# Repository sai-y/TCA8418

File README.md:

# TCA8418

My first PCB design based on Sparkfun's Qwiic connector system. It is an I<sup>2</sup>C based keypad controller. It is inspired by this [one](https://www.sparkfun.com/products/14660).

This repository contains the PCB design for now. Code coming soon.

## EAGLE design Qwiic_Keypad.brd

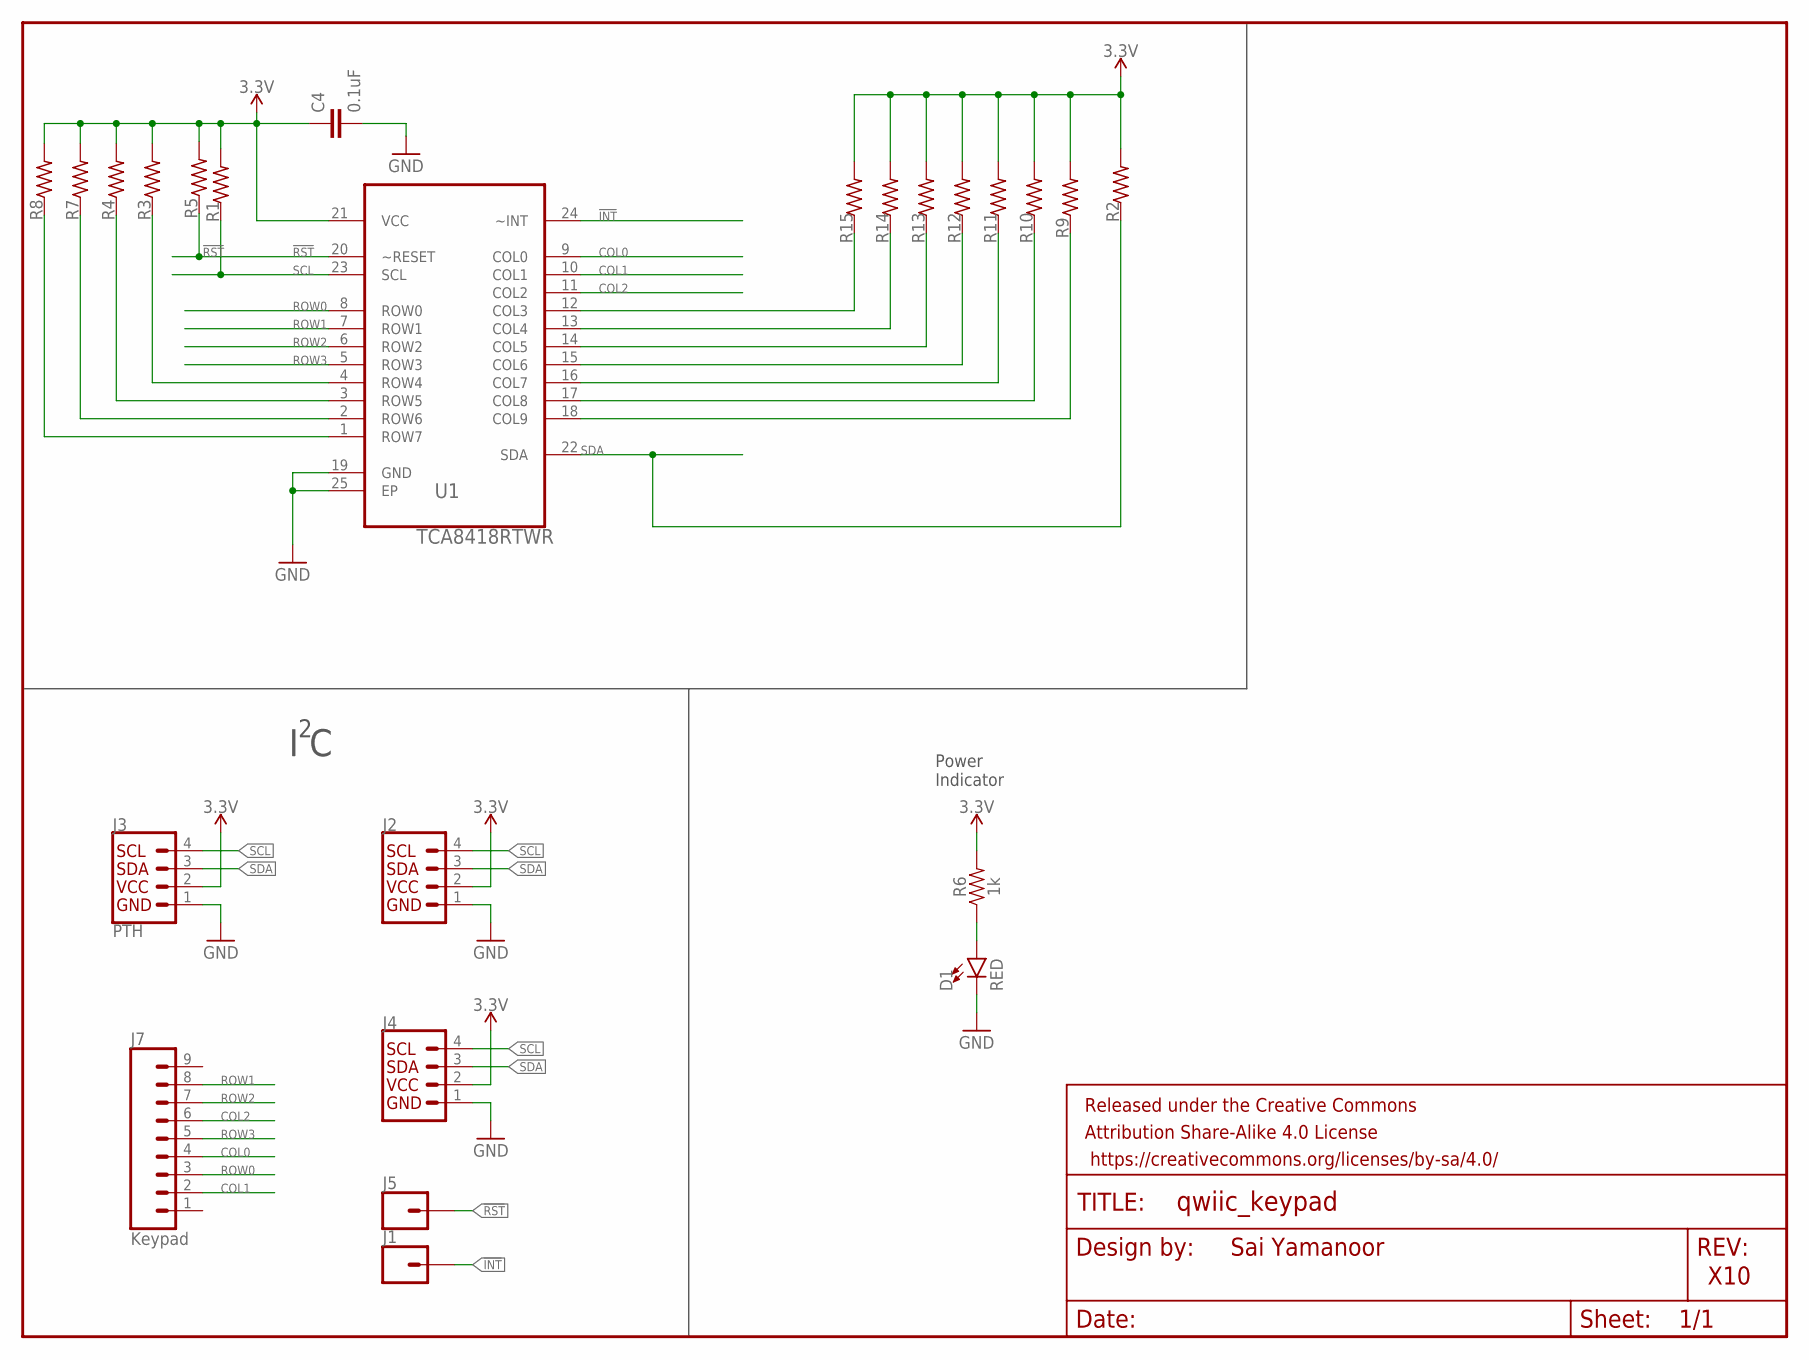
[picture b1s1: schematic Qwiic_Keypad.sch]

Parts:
C4: 0.1uF; 0603
D1: RED; LED-0603
FRAME1: FRAME-LETTER; CREATIVE_COMMONS
J1, J5: CONN_01PTH_NO_SILK_YES_STOP; 1X01_NO_SILK
J2, J4: QWIIC_CONNECTORJS-1MM; 1X04_1MM_RA
J3: PTH; 1X04_NO_SILK
J7: Keypad; 1X09_NO_SILK
R1, R2: 4.7k; R0402
R3, R4, R5, R7, R8, R9, R10, R11, R12, R13, R14, R15: 10k; R0402
R6: 1k; 0603
U1: TCA8418RTWR; QFN50P400X400X80-25N

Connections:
3.3V: C4.1, J2.2, J3.2 (VCC), J4.2, R1.2, R2.2, R3.2, R4.2, R5.2, R6.2, R7.2, R8.2, R9.2, R10.2, R11.2, R12.2, R13.2, R14.2, R15.2, U1.21 (VCC)
!INT: J1.1, U1.24 (~INT)
!RST: J5.1, R5.1, U1.20 (~RESET)
COL0: J7.4, U1.9 (COL0)
COL1: J7.2, U1.10 (COL1)
COL2: J7.6, U1.11 (COL2)
GND: C4.2, D1.C, J2.1, J3.1 (GND), J4.1, U1.19 (GND), U1.25 (EP)
unnamed: D1.A, R6.1
unnamed: R3.1, U1.4 (ROW4)
unnamed: R4.1, U1.3 (ROW5)
unnamed: R7.1, U1.2 (ROW6)
unnamed: R8.1, U1.1 (ROW7)
unnamed: R15.1, U1.12 (COL3)
unnamed: R13.1, U1.14 (COL5)
unnamed: R14.1, U1.13 (COL4)
unnamed: R12.1, U1.15 (COL6)
unnamed: R11.1, U1.16 (COL7)
unnamed: R10.1, U1.17 (COL8)
unnamed: R9.1, U1.18 (COL9)
ROW0: J7.3, U1.8 (ROW0)
ROW1: J7.8, U1.7 (ROW1)
ROW2: J7.7, U1.6 (ROW2)
ROW3: J7.5, U1.5 (ROW3)
SCL: J2.4, J3.4 (SCL), J4.4, R1.1, U1.23 (SCL)
SDA: J2.3, J3.3 (SDA), J4.3, R2.1, U1.22 (SDA)

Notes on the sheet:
Sai Yamanoor
X10
I C
Power Indicator

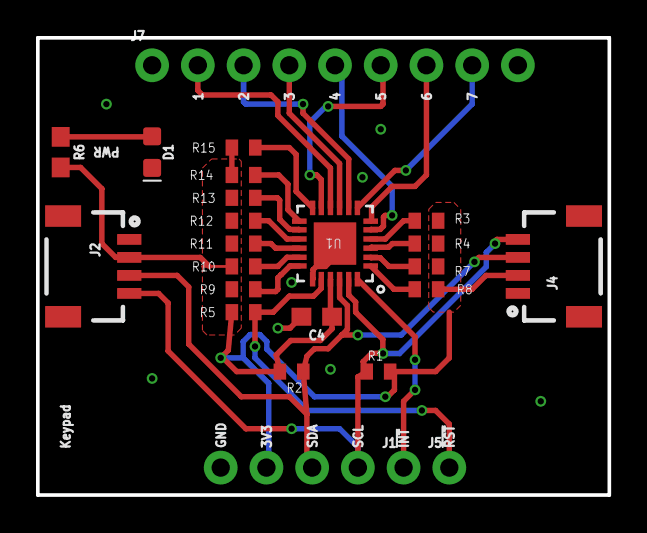
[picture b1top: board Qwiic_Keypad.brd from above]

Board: 2 copper layers, 31.8 x 25.4 mm, 25 parts (0 on the bottom side), 25 nets.

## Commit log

2018-05-18 Checking in repo
2018-05-18 Qwiic keypad
2018-05-18 Adding image
2018-05-18 renaming file

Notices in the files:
parts and their libraries:
SparkFun-Resistors: Licensing: Creative Commons ShareAlike 4.0 International - https://creativecommons.org/licenses/by-sa/4.0
SparkFun-Aesthetics: Released under the Creative Commons Attribution Share-Alike 4.0 License
SparkFun-Aesthetics: https://creativecommons.org/licenses/by-sa/4.0
